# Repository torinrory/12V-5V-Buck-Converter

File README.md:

# 12V-to-5V 3A Synchronous DC-DC Buck Converter (TPS54302)

**Author:** Torin Hamilton  
**CAD Tool:** KiCad 10.0  
**Topology:** Fixed-Frequency ($400\text{ kHz}$) Peak-Current-Mode Synchronous Buck Converter  
**Board Dimensions:** $45\text{ mm} \times 30\text{ mm}$, 2-Layer FR-4 ($1.6\text{ mm}$ thickness, $1\text{ oz}$ copper)

---

## 1. Project Overview

This project implements a compact, high-efficiency **12V-to-5V, 3A Synchronous Step-Down (Buck) DC-DC Converter** based on the Texas Instruments **`TPS54302`** (`SOT-23-6`). It is designed for 12V/24V distributed power buses, embedded systems, and benchtop prototyping, with all surface-mount and through-hole footprints selected and spaced for reliable hand-soldering and oscilloscope characterization.

### Key Electrical Specifications

| Parameter | Symbol | Value | Notes |
| :--- | :---: | :---: | :--- |
| **Input Voltage Range** | $V_{\text{IN}}$ | $8\text{ V} \text{ to } 28\text{ V}$ | Optimized for $12\text{ V}$ nominal input |
| **Output Voltage** | $V_{\text{OUT}}$ | $5.08\text{ V}$ ($5.0\text{ V}$ nom) | Set by $1\%$ feedback divider ($R_2, R_3$) |
| **Max Continuous Output Current** | $I_{\text{OUT(MAX)}}$ | $3.0\text{ A}$ | Integrated $85\text{ m}\Omega$ HS / $40\text{ m}\Omega$ LS MOSFETs |
| **Switching Frequency** | $f_{\text{SW}}$ | $400\text{ kHz}$ | With $\pm 6\%$ frequency spread-spectrum for EMI reduction |
| **Peak Efficiency** | $\eta$ | $\approx 93\% \text{ -- } 95\%$ | At $V_{\text{IN}} = 12\text{ V}, V_{\text{OUT}} = 5\text{ V}$ |
| **Output Voltage Ripple** | $\Delta V_{\text{OUT}}$ | $< 30\text{ mV}_{\text{PP}}$ | Low-ESR MLCC output filter ($2 \times 22\,\mu\text{F}$) |
| **Transient Response ($1.5\text{ A}$ step)** | $\Delta V_{\text{TR}}$ | $< \pm 5\%$ ($\pm 250\text{ mV}$) | Phase-margin boosted via $75\text{ pF}$ feedforward cap |

### Repository Contents
- **[12V_5V_Buck_Converter.pdf](12V_5V_Buck_Converter.pdf)** — Exported PDF Schematic with engineering callouts
- **[12V_5V_Buck_Converter.kicad_sch](12V_5V_Buck_Converter.kicad_sch)** — KiCad 10 Schematic Capture (0 ERC violations)
- **[12V_5V_Buck_Converter.kicad_pcb](12V_5V_Buck_Converter.kicad_pcb)** — KiCad 10 2-Layer PCB Layout (0 DRC violations)
- **[BOM.csv](BOM.csv)** — Orderable Bill of Materials with Manufacturer Part Numbers (DigiKey / Mouser ready)
- **[gerbers/](gerbers/)** — Complete RS-274X Gerber & Excellon Drill package ready for PCB fabrication

---

## 2. Engineering Design & Component Calculations

All component values are derived from the [Texas Instruments TPS54302 Datasheet](tps54302.pdf) (Section 7.2, Pages 14–18).

### 2.1 Output Voltage Set Point ($R_2, R_3$)
The `TPS54302` regulates the feedback pin (`FB`, Pin 4) to an internal bandgap reference of $V_{\text{ref}} = 0.596\text{ V}$ (typical). Using $R_2 = 100\text{ k}\Omega$ ($1\%$) for the upper divider resistor and $R_3 = 13.3\text{ k}\Omega$ ($1\%$) for the lower divider resistor:

$$V_{\text{OUT}} = V_{\text{ref}} \times \left(1 + \frac{R_2}{R_3}\right) = 0.596\text{ V} \times \left(1 + \frac{100\text{ k}\Omega}{13.3\text{ k}\Omega}\right) = 5.077\text{ V}$$

A $49.9\,\Omega$ resistor ($R_1$) is placed in series between $V_{\text{OUT}}$ and the top of the feedback network to provide an injection point for control-loop Bode plot / stability measurements.

### 2.2 Programmable Input Undervoltage Lockout ($R_4, R_5$)
Resistors $R_4 = 511\text{ k}\Omega$ ($1\%$) and $R_5 = 105\text{ k}\Omega$ ($1\%$) form an external voltage divider on the `EN` pin (Pin 5) working with the internal pull-up current ($I_p = 0.7\,\mu\text{A}$) and hysteresis current ($I_h = 1.55\,\mu\text{A}$) to prevent brownout chatter during startup and shutdown:
- **Rising Turn-On Threshold ($V_{\text{EN(rising)}} = 1.23\text{ V}$):**
  $$V_{\text{START}} = V_{\text{EN(rising)}} \left(1 + \frac{R_4}{R_5}\right) - I_p R_4 \approx 6.86\text{ V}$$
- **Falling Turn-Off Threshold ($V_{\text{EN(falling)}} = 1.16\text{ V}$):**
  $$V_{\text{STOP}} = V_{\text{EN(falling)}} \left(1 + \frac{R_4}{R_5}\right) - (I_p + I_h) R_4 \approx 5.65\text{ V}$$

### 2.3 Output Inductor Selection ($L_1$)
For a target inductor ripple ratio $K_{\text{IND}} = 0.35$ up to $V_{\text{IN(MAX)}} = 28\text{ V}$ at $f_{\text{SW}} = 400\text{ kHz}$:

$$L_{\text{MIN}} = \frac{V_{\text{OUT}} \times (V_{\text{IN(MAX)}} - V_{\text{OUT}})}{V_{\text{IN(MAX)}} \times K_{\text{IND}} \times I_{\text{OUT}} \times f_{\text{SW}}} = \frac{5 \times (28 - 5)}{28 \times 0.35 \times 3 \times 400\times 10^3} = 9.78\,\mu\text{H}$$

Selecting the standard value **$L_1 = 10\,\mu\text{H}$** (`Bourns SRP7028A-100M`):
- **Inductor Ripple Current at $V_{\text{IN}} = 12\text{ V}$:**
  $$\Delta I_L = \frac{V_{\text{OUT}} \times (V_{\text{IN}} - V_{\text{OUT}})}{V_{\text{IN}} \times L_1 \times f_{\text{SW}}} = \frac{5 \times (12 - 5)}{12 \times 10\,\mu\text{H} \times 400\text{ kHz}} = 0.729\text{ A}_{\text{PP}}$$
- **Peak Inductor Current ($I_{L(\text{PK})}$):**
  $$I_{L(\text{PK})} = I_{\text{OUT(MAX)}} + \frac{\Delta I_L}{2} \approx 3.36\text{ A} \quad (\text{ at } 12\text{ V}) \quad / \quad 3.51\text{ A} \quad (\text{ at } 28\text{ V})$$
- **Selected Inductor Margins:** The `Bourns SRP7028A-100M` shielded power inductor is rated for **$I_{\text{RMS}} = 4.5\text{ A}$** and **$I_{\text{sat}} = 8.0\text{ A}$**, providing $>2\times$ saturation margin against core saturation during load transients.

### 2.4 Input & Output Capacitor Selection ($C_1\text{--}C_6$)
- **Input Decoupling ($C_1 = 10\,\mu\text{F}, 50\text{ V X7R}$ & $C_2 = 0.1\,\mu\text{F}, 50\text{ V X7R}$):**
  - Worst-case input RMS ripple current is $I_{\text{CIN(RMS)}} \approx I_{\text{OUT(MAX)}} / 2 = 1.5\text{ A}$.
  - $C_1$ ($1206$ package, $50\text{ V}$ X7R) provides bulk charge storage with minimal DC-bias derating at $12\text{ V}$, while $C_2$ ($0805$) is placed immediately adjacent to `U1` Pin 3 (`VIN`) and Pin 1 (`GND`) to shunt high-$di/dt$ switching currents.
- **Bootstrap Capacitor ($C_3 = 0.1\,\mu\text{F}, 50\text{ V X7R}$):**
  - Connected between `BOOT` (Pin 6) and `SW` (Pin 2) to supply the floating gate drive for the integrated high-side N-channel MOSFET.
- **Output Filter Capacitors ($C_4, C_5 = 2 \times 22\,\mu\text{F}, 25\text{ V X5R/X7R}$):**
  - To contain a $1.5\text{ A}$ load transient within $\Delta V_{\text{OUT}} = \pm 5\%$ ($0.25\text{ V}$), the minimum required effective output capacitance is:
    $$C_{\text{OUT(MIN)}} > \frac{2 \times \Delta I_{\text{OUT}}}{f_{\text{SW}} \times \Delta V_{\text{OUT}}} = \frac{2 \times 1.5\text{ A}}{400\text{ kHz} \times 0.25\text{ V}} = 30\,\mu\text{F}$$
  - Using two parallel $22\,\mu\text{F}$, $25\text{ V}$ `1206` ceramic capacitors ($44\,\mu\text{F}$ nominal) accounts for MLCC DC-bias derating at $5\text{ V}$ while halving equivalent series resistance (ESR) and ESL.
- **Feedforward Compensation Capacitor ($C_6 = 75\text{ pF}, 50\text{ V C0G/NP0}$):**
  - Placed in parallel with $R_2$ to introduce a phase-lead zero near the control loop crossover frequency ($f_0 \approx \frac{5.1}{V_{\text{OUT}} \times C_{\text{OUT}}} \approx 23\text{ kHz}$), boosting phase margin with low-ESR ceramic output capacitors:
    $$C_6 \approx \frac{1}{2\pi f_0 R_2} \approx 75\text{ pF}$$

---

## 3. PCB Layout & EMI Mitigation Architecture

Switching regulators involve high-$di/dt$ current loops ($400\text{ kHz}$ square-wave switching up to $3\text{ A}$). The 2-layer PCB ([12V_5V_Buck_Converter.kicad_pcb](12V_5V_Buck_Converter.kicad_pcb)) follows Texas Instruments' layout guidelines (Datasheet Section 7.4):

1. **Minimized High-$di/dt$ Input Hot Loop:** `C2` ($0.1\,\mu\text{F}$) and `C1` ($10\,\mu\text{F}$) are placed directly beside `U1` Pins 1 (`GND`) and 3 (`VIN`) with a dedicated top-layer `GND` tie and stitching via to the unbroken bottom `GND` plane.
2. **Compact Switching Node (`SW`):** The trace connecting `U1` Pin 2 (`SW`), `L1` Pad 1, and `C3` is kept short and direct on `F.Cu` to minimize parasitic ringing and capacitively coupled radiated EMI.
3. **High-Current Power Routing with Pin Neck-Down:** Power paths (`Vin`, `SW`, `Vout`) are routed with wide **$1.5\text{ mm}$** copper tracks between passives and connectors, necking down to **$0.5\text{ mm}$** only at the fine-pitch ($0.95\text{ mm}$) `SOT-23-6` pads.
4. **Noise-Isolated Feedback Network:** The high-impedance `FB` node (`R1`, `R2`, `R3`, `C6`) is grouped tightly next to `U1` Pin 4 on the opposite side of the IC from the inductor and `SW` node.
5. **Dual-Layer Ground Planes & Thermal Relief:** Both `F.Cu` and `B.Cu` are poured with `GND` zones (`0.3 mm` clearance and thermal-relief spokes for hand-solderability) stitched with through-hole vias.

---

## 4. Bill of Materials (BOM)

The full spreadsheet is available in [BOM.csv](BOM.csv).

| Ref | Qty | Value | Package | Manufacturer | MPN | Description |
| :--- | :-: | :--- | :--- | :--- | :--- | :--- |
| `U1` | 1 | `TPS54302` | `SOT-23-6` | Texas Instruments | `TPS54302DDCR` | 4.5V–28V In, 3A Sync Buck Converter |
| `L1` | 1 | `10uH` | `7.3x6.6mm` | Bourns | `SRP7028A-100M` | Shielded Power Inductor, $4.5\text{ A}\_{\text{RMS}}$, $8\text{ A}\_{\text{sat}}$ |
| `C1` | 1 | `10uF` | `1206` | Samsung | `CL31B106KBHNNNE` | MLCC $10\,\mu\text{F}$, $50\text{ V}$, X7R, $\pm 10\%$ |
| `C2, C3` | 2 | `0.1uF` | `0805` | Yageo | `CC0805KRX7R9BB104` | MLCC $0.1\,\mu\text{F}$, $50\text{ V}$, X7R, $\pm 10\%$ |
| `C4, C5` | 2 | `22uF` | `1206` | Murata | `GRM31CR61E226KE15L` | MLCC $22\,\mu\text{F}$, $25\text{ V}$, X5R, $\pm 10\%$ |
| `C6` | 1 | `75pF` | `0805` | Murata | `GRM2165C1H750JA01D` | MLCC $75\text{ pF}$, $50\text{ V}$, C0G/NP0, $\pm 5\%$ |
| `R1` | 1 | `49.9` | `0805` | Yageo | `RC0805FR-0749R9L` | Thick Film Resistor $49.9\,\Omega$, $1\%$, $1/8\text{ W}$ |
| `R2` | 1 | `100k` | `0805` | Yageo | `RC0805FR-07100KL` | Thick Film Resistor $100\text{ k}\Omega$, $1\%$, $1/8\text{ W}$ |
| `R3` | 1 | `13.3k` | `0805` | Yageo | `RC0805FR-0713K3L` | Thick Film Resistor $13.3\text{ k}\Omega$, $1\%$, $1/8\text{ W}$ |
| `R4` | 1 | `511k` | `0805` | Yageo | `RC0805FR-07511KL` | Thick Film Resistor $511\text{ k}\Omega$, $1\%$, $1/8\text{ W}$ |
| `R5` | 1 | `105k` | `0805` | Yageo | `RC0805FR-07105KL` | Thick Film Resistor $105\text{ k}\Omega$, $1\%$, $1/8\text{ W}$ |
| `R6` | 1 | `1k` | `0805` | Yageo | `RC0805FR-071KL` | Thick Film Resistor $1\text{ k}\Omega$, $1\%$, $1/8\text{ W}$ |
| `D1` | 1 | `Green` | `0805` | Lite-On | `LTST-C170KGKT` | Green SMD LED ($571\text{ nm}, V_F = 2.0\text{ V}$) |
| `J1, J2` | 2 | `Screw Term` | `1x02 P5.08mm` | Phoenix Contact | `1715721` | 2-Pin Terminal Block, $5.08\text{ mm}$, $17.5\text{ A}$ |
| `TP1–TP4` | 4 | `Test Point` | `D1.5mm` PTH | Keystone | `5005` *(or DNP)* | Test Point Loop ($0.7\text{ mm}$ drill) or bare PTH |

---

## 5. Hand-Soldering & Bench Bring-Up Guide

### Recommended Soldering Order (Lowest to Highest Profile)
1. **Regulator IC (`U1` - `TPS54302`):** Verify the Pin 1 dot/bevel aligns with the top-left pad (`GND`, marked by the silkscreen triangle). Tack one corner pin with flux and fine solder, verify alignment, then solder the remaining 5 pins.
2. **0805 Passives & LED (`C2`, `C3`, `C6`, `R1`–`R6`, `D1`):** Note that `D1` is polarized—align the green cathode marking on the LED with **Pad 1 (`GND`, left pad)**.
3. **1206 Input/Output Capacitors (`C1`, `C4`, `C5`).**
4. **Power Inductor (`L1` - `SRP7028A-100M`):** Pre-tin one pad, reflow while sliding the inductor into place, then solder the second pad generously.
5. **Through-Hole Screw Terminals (`J1`, `J2`) & Test Points (`TP1`–`TP4`).**

### Safe First Power-Up Checklist
1. **Visual & Continuity Check (Power Off):**
   - Measure resistance across `J1` (`+12V` to `GND`) and `J2` (`+5V 3A` to `GND`) with a digital multimeter (DMM) to confirm there are no solder bridges or shorts to `GND`.
2. **Current-Limited No-Load Test:**
   - Set a bench DC power supply to **$12.0\text{ V}$** with a **$100\text{ mA}$ current limit** and connect to `J1`.
   - Turn on the output: the green indicator LED (`D1`) should illuminate, input current draw should be $< 10\text{ mA}$ at no load, and `TP3` (`Vout`) to `TP4` (`GND`) should read **$5.05\text{ V} \text{ -- } 5.10\text{ V}$**.
3. **Oscilloscope Switching & Ripple Verification:**
   - Increase the supply current limit to **$2.0\text{ A}$**, connect an electronic load (or power resistor) to `J2`, and probe `TP2` (`SW`) and `TP3` (`Vout` AC-coupled) to observe the $400\text{ kHz}$ switching waveform and $< 30\text{ mV}_{\text{PP}}$ output ripple.

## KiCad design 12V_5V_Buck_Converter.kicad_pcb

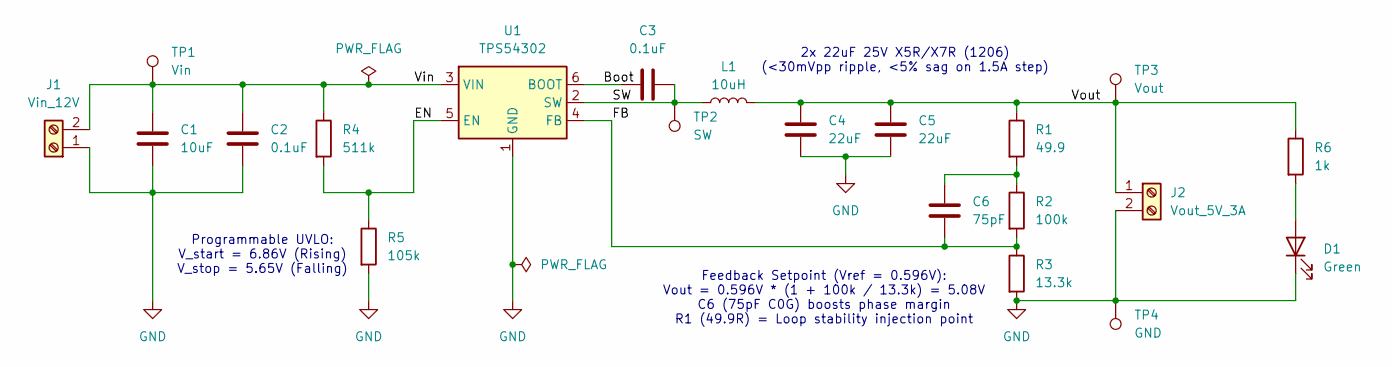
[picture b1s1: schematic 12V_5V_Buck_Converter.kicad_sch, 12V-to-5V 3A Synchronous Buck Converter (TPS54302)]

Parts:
C1: 10uF; C_1206_3216Metric_Pad1.33x1.80mm_HandSolder
C2, C3: 0.1uF; C_0805_2012Metric_Pad1.18x1.45mm_HandSolder
C4, C5: 22uF; C_1206_3216Metric_Pad1.33x1.80mm_HandSolder
C6: 75pF; C_0805_2012Metric_Pad1.18x1.45mm_HandSolder
D1: Green; LED_0805_2012Metric_Pad1.15x1.40mm_HandSolder
J1: Vin_12V; TerminalBlock_Phoenix_MKDS-1,5-2-5.08_1x02_P5.08mm_Horizont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
J2: Vout_5V_3A; TerminalBlock_Phoenix_MKDS-1,5-2-5.08_1x02_P5.08mm_Horizont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
L1: 10uH; L_Bourns_SRP7028A_7.3x6.6mm
R1: 49.9; R_0805_2012Metric_Pad1.20x1.40mm_HandSolder
R2: 100k; R_0805_2012Metric_Pad1.20x1.40mm_HandSolder
R3: 13.3k; R_0805_2012Metric_Pad1.20x1.40mm_HandSolder
R4: 511k; R_0805_2012Metric_Pad1.20x1.40mm_HandSolder
R5: 105k; R_0805_2012Metric_Pad1.20x1.40mm_HandSolder
R6: 1k; R_0805_2012Metric_Pad1.20x1.40mm_HandSolder
TP1: Vin; TestPoint_THTPad_D1.5mm_Drill0.7mm
TP2: SW; TestPoint_THTPad_D1.5mm_Drill0.7mm
TP3: Vout; TestPoint_THTPad_D1.5mm_Drill0.7mm
TP4: GND; TestPoint_THTPad_D1.5mm_Drill0.7mm
U1: TPS54302; SOT-23-6

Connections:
/Boot: C3.1, U1.6 (BOOT)
/EN: R4.2, R5.1, U1.5 (EN)
/FB: C6.2, R2.2, R3.1, U1.4 (FB)
/SW: C3.2, L1.1, TP2.1 (1_1), U1.2 (SW)
/Vin: C1.1, C2.1, J1.2, R4.1, TP1.1 (1_1), U1.3 (VIN)
/Vout: C4.2, C5.1, J2.1, L1.2, R1.1, R6.1, TP3.1 (1_1)
GND: C1.2, C2.2, C4.1, C5.2, D1.1 (K), J1.1, J2.2, R3.2, R5.2, TP4.1 (1_1), U1.1 (GND)
unnamed: C6.1, R1.2, R2.1
unnamed: D1.2 (A), R6.2

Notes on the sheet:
Programmable UVLO: V_start = 6.86V (Rising) V_stop = 5.65V (Falling)
2x 22uF 25V X5R/X7R (1206) (<30mVpp ripple, <5% sag on 1.5A step)
Feedback Setpoint (Vref = 0.596V): Vout = 0.596V * (1 + 100k / 13.3k) = 5.08V C6 (75pF C0G) boosts phase margin R1 (49.9R) = Loop stability injection point

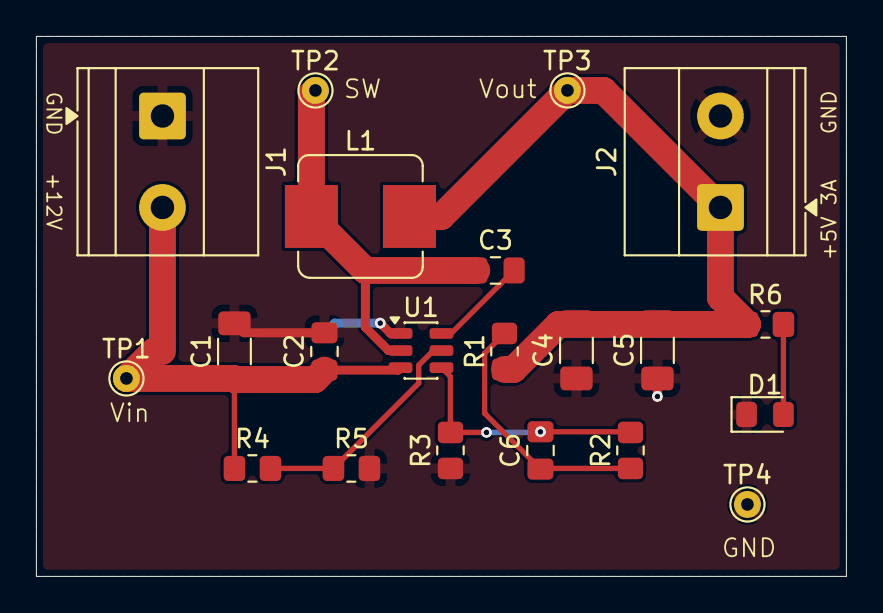
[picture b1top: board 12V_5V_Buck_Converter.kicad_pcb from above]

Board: 2 copper layers, 45.0 x 30.0 mm, 21 parts (0 on the bottom side), 9 nets.

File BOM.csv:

Item,Reference,Qty,Value,Description,Package / KiCad Footprint,Manufacturer,Manufacturer Part Number (MPN),Alternate MPN,Key Specifications & Engineering Notes
1,U1,1,TPS54302,"IC REG BUCK SYNC 5V 3A SOT23-6",Package_TO_SOT_SMD:SOT-23-6,Texas Instruments,TPS54302DDCR,TPS54302DDCT,"4.5V-28V Input, 3A Continuous Output, 400kHz Synchronous Step-Down Converter (integrated 85mOhm/40mOhm FETs)"
2,L1,1,10uH,"Shielded Molded Power Inductor 10uH 4.5A",Inductor_SMD:L_Bourns_SRP7028A_7.3x6.6mm,Bourns,SRP7028A-100M,SRP7050TA-100M,"10uH +/-20%, I_rms = 4.5A, I_sat = 8.0A, DCR = 53.5mOhm max, 7.3x6.6mm SMD"
3,C1,1,10uF,"Input Bulk Ceramic Capacitor 10uF 50V X7R",Capacitor_SMD:C_1206_3216Metric_Pad1.33x1.80mm_HandSolder,Samsung Electro-Mechanics,CL31B106KBHNNNE,GRM31CR71H106KA12L,"10uF +/-10%, 50V (exceeds TI 35V min recommendation), X7R Dielectric, 1206"
4,"C2, C3",2,0.1uF,"HF Input Bypass & Bootstrap Capacitor 0.1uF 50V X7R",Capacitor_SMD:C_0805_2012Metric_Pad1.18x1.45mm_HandSolder,Yageo,CC0805KRX7R9BB104,CL21B104KBCNNNC,"0.1uF (100nF) +/-10%, 50V, X7R Dielectric, 0805 (C2 = VIN HF Bypass, C3 = BOOT-SW Charge Pump)"
5,"C4, C5",2,22uF,"Output Filter Ceramic Capacitor 22uF 25V X5R/X7R",Capacitor_SMD:C_1206_3216Metric_Pad1.33x1.80mm_HandSolder,Murata Electronics,GRM31CR61E226KE15L,CL31A226KAHNNNE,"22uF +/-10%, 25V (minimizes DC bias derating at 5V), X5R/X7R Dielectric, 1206 (44uF nominal total)"
6,C6,1,75pF,"Feedforward Compensation Capacitor 75pF 50V C0G/NP0",Capacitor_SMD:C_0805_2012Metric_Pad1.18x1.45mm_HandSolder,Murata Electronics,GRM2165C1H750JA01D,CC0805JRNPO9BN750,"75pF +/-5%, 50V, C0G/NP0 Dielectric, 0805 (boosts control loop phase margin at crossover)"
7,R1,1,49.9,"Control Loop Injection Resistor 49.9 Ohm 1%",Resistor_SMD:R_0805_2012Metric_Pad1.20x1.40mm_HandSolder,Yageo,RC0805FR-0749R9L,CRCW080549R9FKTA,"49.9 Ohm +/-1%, 0.125W (1/8W), Thick Film, 0805 (Bode plot / stability test injection point)"
8,R2,1,100k,"Upper Feedback Divider Resistor 100k Ohm 1%",Resistor_SMD:R_0805_2012Metric_Pad1.20x1.40mm_HandSolder,Yageo,RC0805FR-07100KL,CRCW0805100KFKEA,"100k Ohm +/-1%, 0.125W (1/8W), Thick Film, 0805 (sets Vout = 5.08V with R3 = 13.3k)"
9,R3,1,13.3k,"Lower Feedback Divider Resistor 13.3k Ohm 1%",Resistor_SMD:R_0805_2012Metric_Pad1.20x1.40mm_HandSolder,Yageo,RC0805FR-0713K3L,CRCW080513K3FKEA,"13.3k Ohm +/-1%, 0.125W (1/8W), Thick Film, 0805 (sets Vout = 5.08V with R2 = 100k)"
10,R4,1,511k,"Upper UVLO Enable Divider Resistor 511k Ohm 1%",Resistor_SMD:R_0805_2012Metric_Pad1.20x1.40mm_HandSolder,Yageo,RC0805FR-07511KL,CRCW0805511KFKEA,"511k Ohm +/-1%, 0.125W (1/8W), Thick Film, 0805 (sets Vin UVLO start/stop thresholds)"
11,R5,1,105k,"Lower UVLO Enable Divider Resistor 105k Ohm 1%",Resistor_SMD:R_0805_2012Metric_Pad1.20x1.40mm_HandSolder,Yageo,RC0805FR-07105KL,CRCW0805105KFKEA,"105k Ohm +/-1%, 0.125W (1/8W), Thick Film, 0805 (sets Vin UVLO start/stop thresholds)"
12,R6,1,1k,"LED Current Limiting Resistor 1k Ohm 1%",Resistor_SMD:R_0805_2012Metric_Pad1.20x1.40mm_HandSolder,Yageo,RC0805FR-071KL,CRCW08051K00FKEA,"1k Ohm +/-1%, 0.125W (1/8W), Thick Film, 0805 (limits D1 indicator LED current to ~3mA at 5V)"
13,D1,1,Green,"5V Power Good Indicator LED Green 0805",LED_SMD:LED_0805_2012Metric_Pad1.15x1.40mm_HandSolder,Lite-On,LTST-C170KGKT,150080GS75000,"Green (571nm) SMD LED, Vf = 2.0V typ, 0805 (Note: Align cathode mark with Pad 1 / GND on PCB)"
14,"J1, J2",2,"Vin_12V, Vout_5V_3A","2-Pos Screw Terminal Block 5.08mm Pitch",TerminalBlock_Phoenix:TerminalBlock_Phoenix_MKDS-1,5-2-5.08_1x02_P5.08mm_Horizontal,Phoenix Contact,1715721,OSTTC022162,"MKDS 1,5/ 2-5,08, 2-Pin 5.08mm Pitch, Through-Hole, Rated 17.5A / 400V, 14-26 AWG"
15,"TP1, TP2, TP3, TP4",4,"Vin, SW, Vout, GND","PCB Test Point Loop (or Probe Bare PTH Directly)",TestPoint:TestPoint_THTPad_D1.5mm_Drill0.7mm,Keystone Electronics,5005,DNP (Bare Pad),"OptionalMiniature THT Test Point for 0.7mm (0.028in) drill, or leave unpopulated to probe plated holes directly"
